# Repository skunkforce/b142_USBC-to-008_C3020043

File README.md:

# edgy_board number b142
This design is part of the [edgy board project](https://github.com/skunkforce/edgy_boards). It provides a waterproof USB 2.0 capable 16 pin USB C connector.

[LCSC Part C3020043](https://lcsc.com/product-detail/USB-Connectors_SHOU-HAN-TYPE-C-16PFS-4J-H7-05-IPX6_C3020043.html)

# getting started
This repository uses submodules. After cloning use the command 

```$ git submodule update --init --recursive```

to pull the submodules before opening the project with kicad. 

# Tests
Tests can be found in [TESTS.md](TESTS.md)

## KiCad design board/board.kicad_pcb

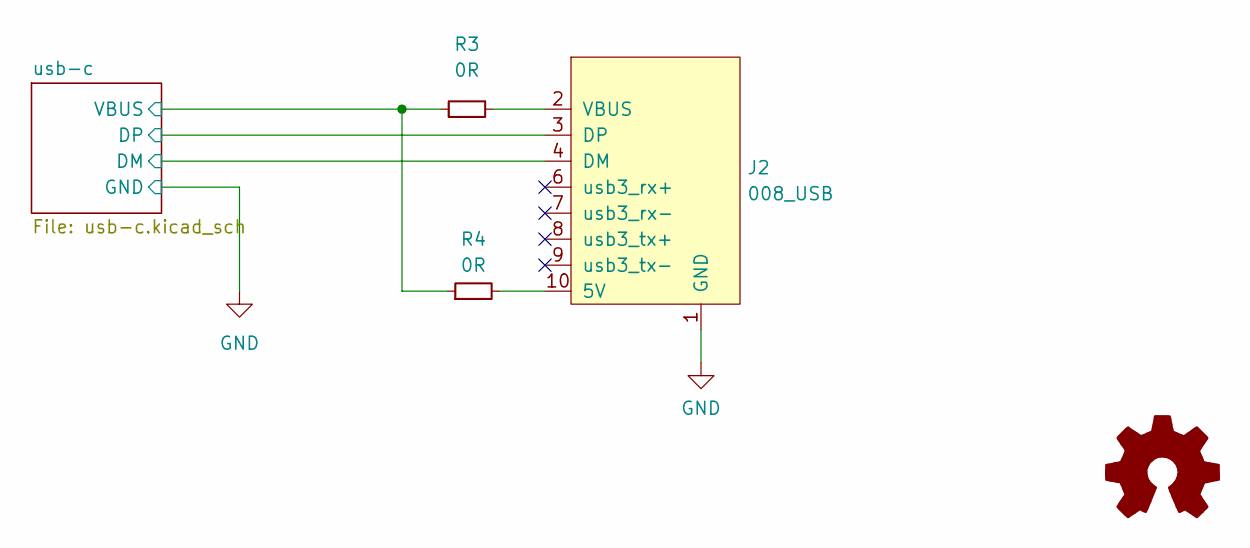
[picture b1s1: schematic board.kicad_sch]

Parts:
J2: 008_USB; on_edge_2x05_host
LOGO1: Logo_Open_Hardware_Small; OSHW-Symbol_6.7x6mm_SilkScreen
R3, R4: 0R; R_0603_1608Metric

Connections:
/usb-c/DM: J2.4 (DM); also elsewhere on the board
/usb-c/DP: J2.3 (DP); also elsewhere on the board
/usb-c/VBUS: R3.1, R4.1; also elsewhere on the board
GND: J2.1 (GND); also elsewhere on the board
unnamed: J2.10 (5V), R4.2
unnamed: J2.2 (VBUS), R3.2

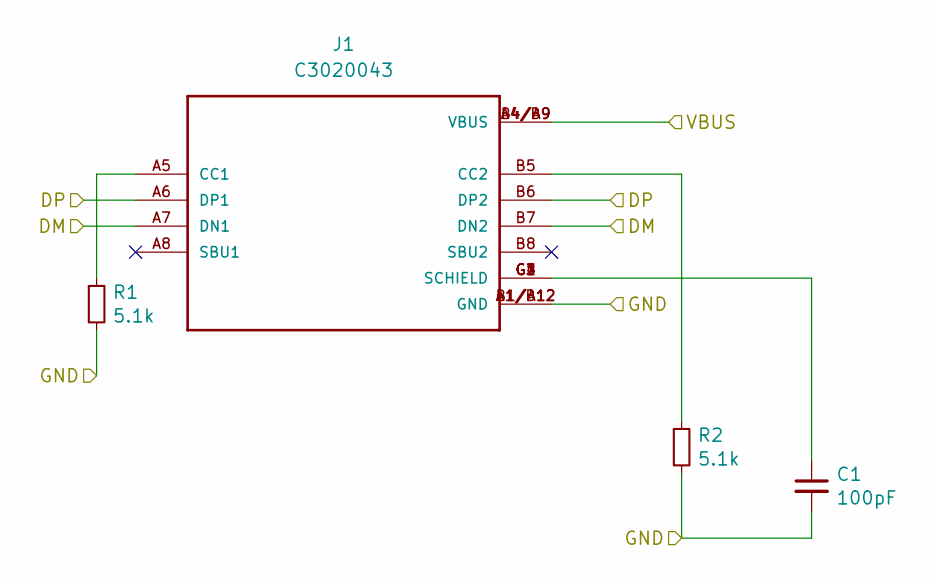
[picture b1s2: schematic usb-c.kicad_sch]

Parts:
C1: 100pF; C_0402_1005Metric; lcsc C14858
J1: C3020043; TYPE-C 16PFS 4J-H7.05 IPX6; lcsc C3020043
R1, R2: 5.1k; R_0402_1005Metric; lcsc C25905

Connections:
/usb-c/DM: J1.A7 (DN1), J1.B7 (DN2); also elsewhere on the board
/usb-c/DP: J1.A6 (DP1), J1.B6 (DP2); also elsewhere on the board
/usb-c/VBUS: J1.A4/B9 (VBUS), J1.B4/A9 (VBUS); also elsewhere on the board
GND: C1.2, J1.A1/B12 (GND), J1.B1/A12 (GND), R1.2, R2.2; also elsewhere on the board
unnamed: C1.1, J1.G1 (SCHIELD), J1.G2 (SCHIELD), J1.G3 (SCHIELD), J1.G4 (SCHIELD)
unnamed: J1.A5 (CC1), R1.1
unnamed: J1.B5 (CC2), R2.1

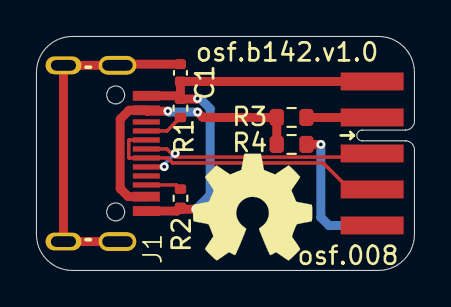
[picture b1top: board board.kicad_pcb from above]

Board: 2 copper layers, 21.0 x 13.0 mm, 8 parts (0 on the bottom side), 9 nets.

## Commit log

2025-07-26 added LCSC Part numbers
